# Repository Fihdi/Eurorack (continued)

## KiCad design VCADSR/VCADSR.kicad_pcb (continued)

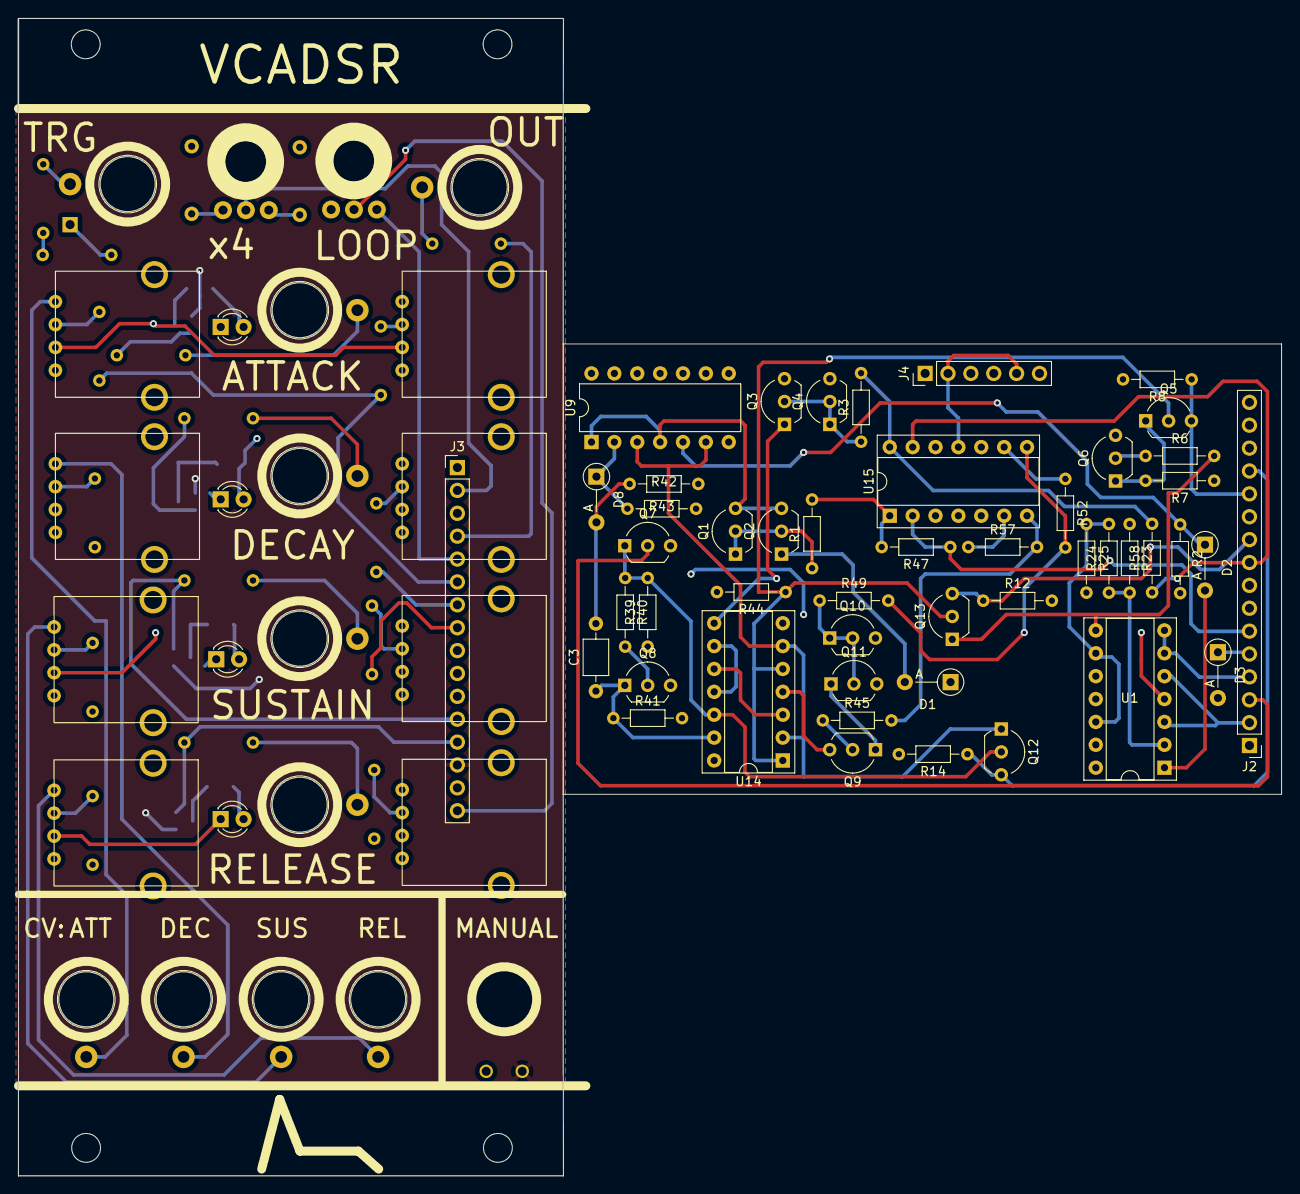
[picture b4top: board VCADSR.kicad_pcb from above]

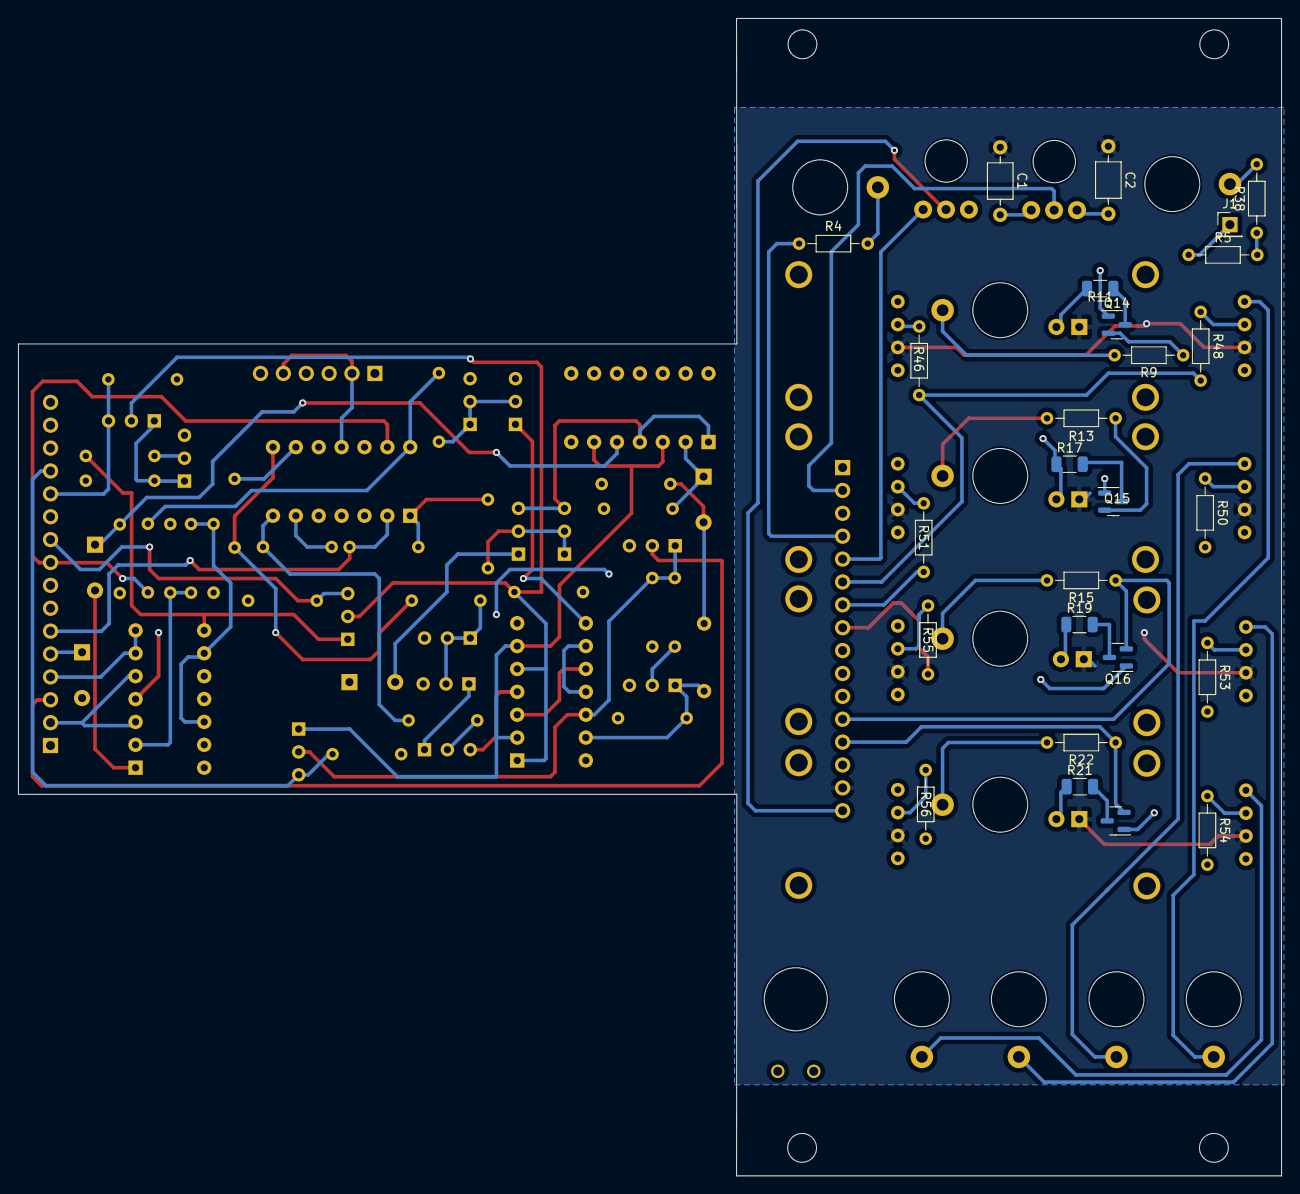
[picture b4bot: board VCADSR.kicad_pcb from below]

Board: 4 copper layers, 140.2 x 128.5 mm, 99 parts (26 on the bottom side), 72 nets.

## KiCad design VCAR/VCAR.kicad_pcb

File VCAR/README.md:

# 10hp Voltage controlled Attack and Release/Slew rate limiter

Voltage controlled SLEW Rate limiter / Attack/Release Module.

Can be used as an Envelope Generator, Slew Rate Limiter, VCO, LFO, Waveshaper, Gate Delay, Rythm Generator and a million other things.

Finally got this one working after 3 Revisions....

Schematic inspired by the legendary Dual Universal Slope Generator by Serge Tcherepnin, and later on Make Noise Maths, Befaco Rampage, Kassutronics Slope, etc.

One thing that could be added would be a jumper at the summing stage for the Rise (Attack) CV so that the feedback signal goes to either the first or second inverting stage ( the second inverter would then also be an inverting summing amplifier). This would give sharkfins instead of exponential spikes.

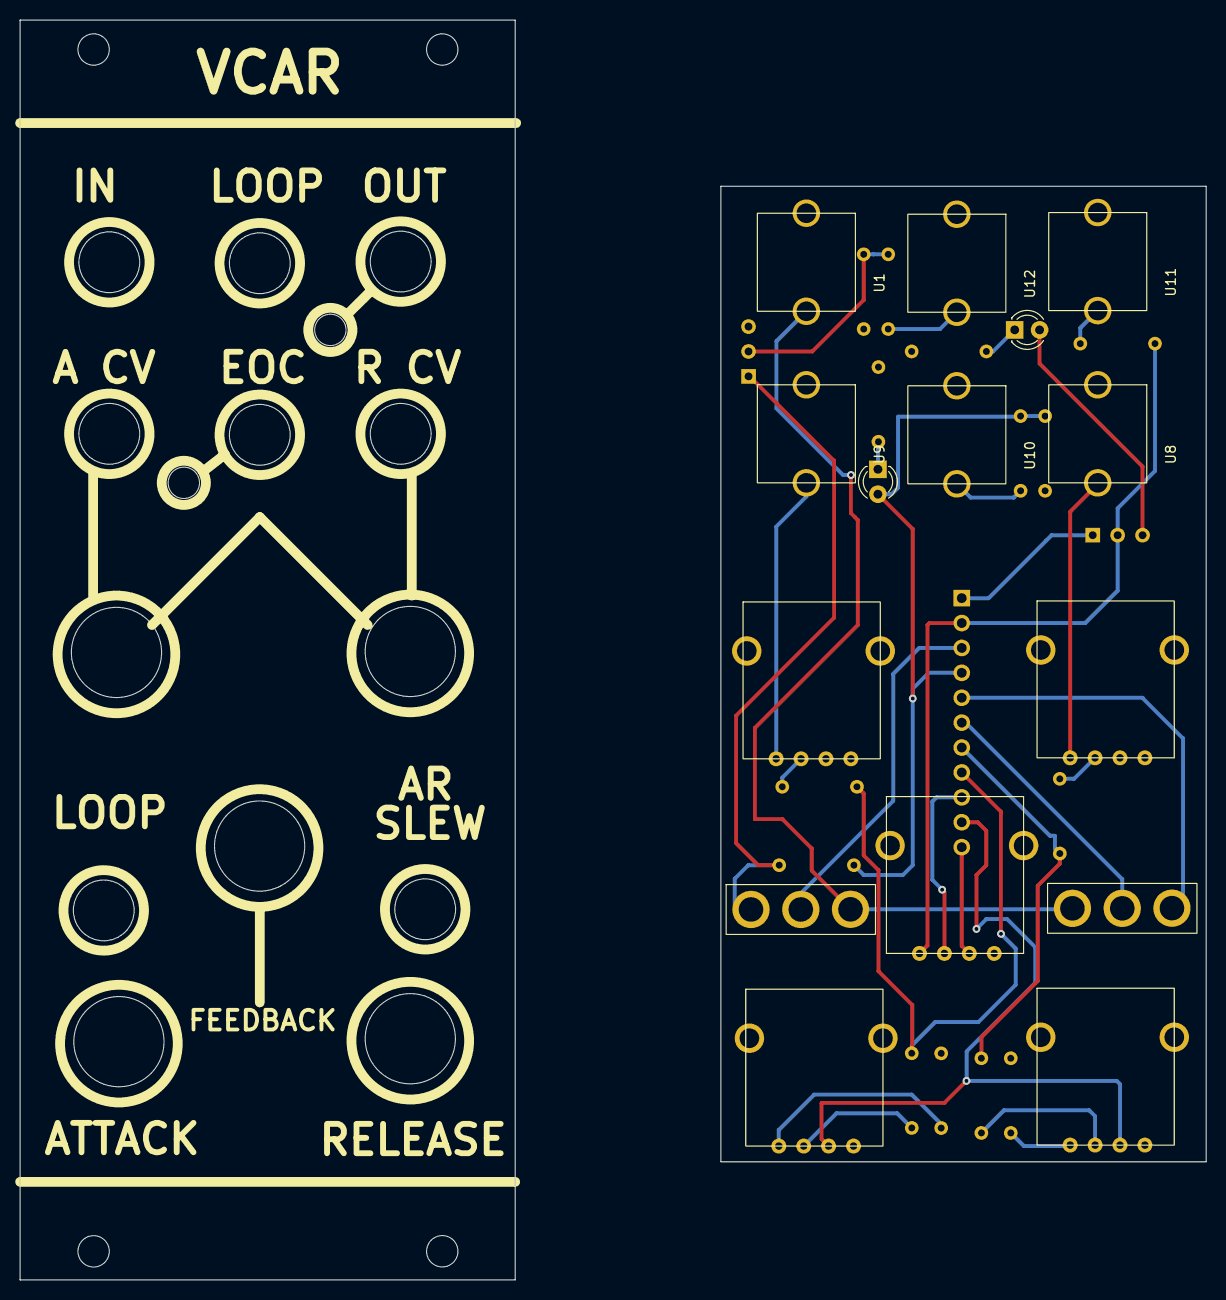
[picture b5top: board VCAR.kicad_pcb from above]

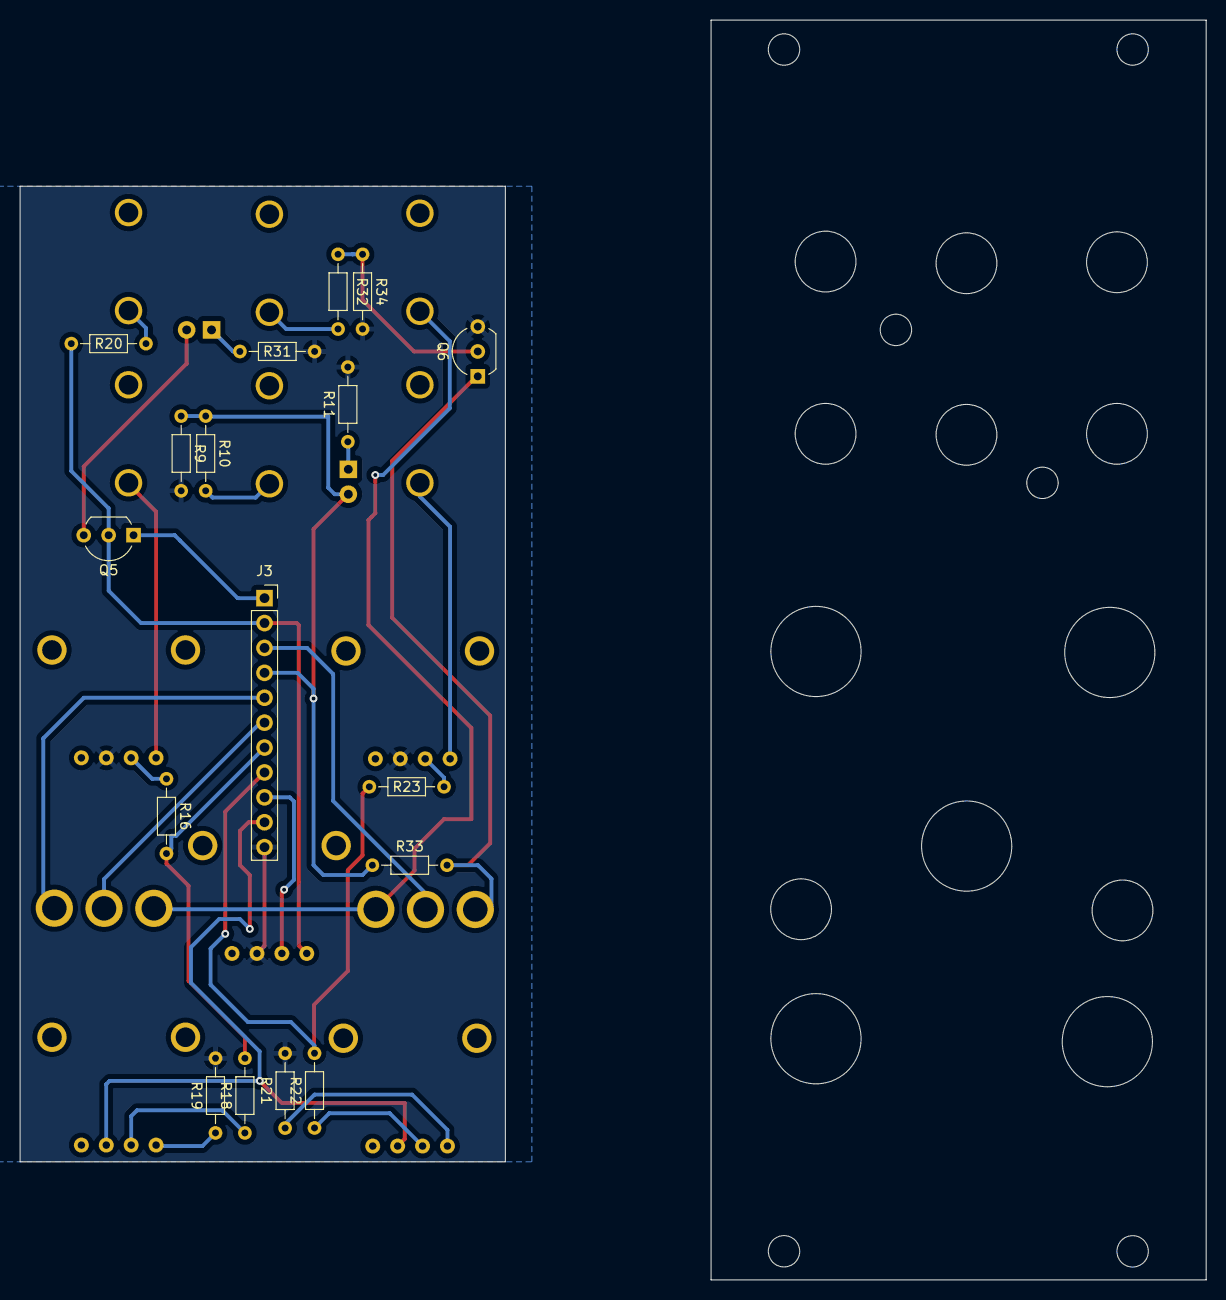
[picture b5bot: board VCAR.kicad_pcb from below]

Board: 2 copper layers, 49.5 x 99.5 mm, 32 parts (17 on the bottom side), 28 nets.

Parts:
D2, D7: LED; LED_D3.0mm
J3: Conn_01x11_Pin; PinSocket_1x11_P2.54mm_Vertical
Q5, Q6: BC547; TO-92_Inline_Wide
R9, R10, R11, R16, R18, R19, R20, R21, R22, R23, R31, R32, R33, R34: R; R_Axial_DIN0204_L3.6mm_D1.6mm_P7.62mm_Horizontal
RV1, RV2, RV3, RV4, RV5: R_Potentiometer; AlpsPot
U1, U8, U9, U10, U11, U12: Aux_flush; 3mm5 Mono Aux
U2, U7: Switch

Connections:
+12V: J3.1, Q5.1 (C)
-12V: J3.10, RV2.3, RV3.3
BUF_IN: J3.3, U7.2
EOC: D2.2 (A), J3.4, R9.1, R10.1, R33.1
FBO: J3.9, RV5.2
FF: J3.5, U2.3
GND: J3.11, Q6.3 (E), R9.2, R11.2, R19.2, R21.2, R31.2, R34.2, RV1.3, RV4.3, RV5.3
GOAL: J3.6, U2.2
IN: U1.1, U2.1, U7.3
unnamed: D2.1 (K), R11.1
unnamed: D7.2 (A), Q5.3 (E)
unnamed: D7.1 (K), R31.1
unnamed: Q6.2 (B), R32.1, R34.1
unnamed: Q6.1 (C), R33.2, U7.1
unnamed: R10.2, U10.1
unnamed: R16.1, RV1.2
unnamed: R18.1, RV2.2
unnamed: R19.1, RV2.1
unnamed: R20.2, U11.1
unnamed: R21.1, RV3.1
unnamed: R22.1, RV3.2
unnamed: R23.1, RV4.2
unnamed: R32.2, U12.1
unnamed: RV1.1, U8.1
unnamed: RV4.1, U9.1
OUT: J3.2, Q5.2 (B), R20.1, RV5.1
VGND1: J3.7, R16.2, R18.2
VGND2: J3.8, R22.2, R23.2

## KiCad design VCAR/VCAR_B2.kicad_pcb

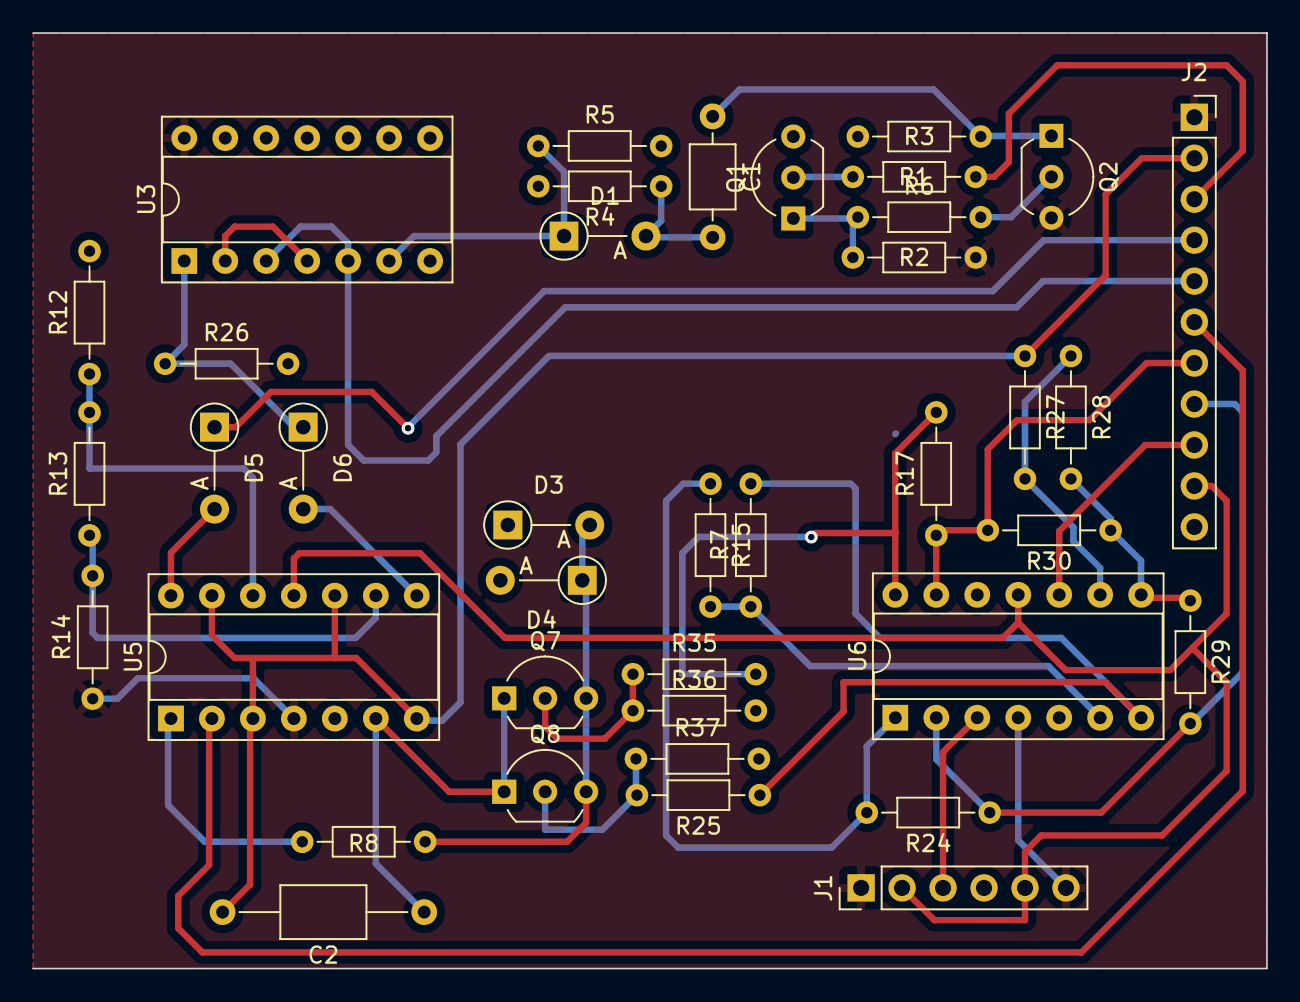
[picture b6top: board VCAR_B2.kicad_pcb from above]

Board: 2 copper layers, 76.5 x 58.0 mm, 39 parts (0 on the bottom side), 34 nets.

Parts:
C1: C; C_Axial_L3.8mm_D2.6mm_P7.50mm_Horizontal
C2: C; C_Axial_L5.1mm_D3.1mm_P12.50mm_Horizontal
D1, D3, D4, D5, D6: D; D_A-405_P5.08mm_Vertical_AnodeUp
J1: Conn_01x06_Pin; PinHeader_1x06_P2.54mm_Vertical
J2: Conn_01x11_Pin; PinSocket_1x11_P2.54mm_Vertical
Q1, Q8: BC547; TO-92_Inline_Wide
Q2, Q7: BC557; TO-92_Inline_Wide
R1, R2, R3, R4, R5, R6, R7, R8, R12, R13, R14, R15, R17, R24, R25, R26, R27, R28, R29, R30, R35, R36, R37: R; R_Axial_DIN0204_L3.6mm_D1.6mm_P7.62mm_Horizontal
U3: 4001; DIP-14_W7.62mm_Socket
U5, U6: TL074; DIP-14_W7.62mm_Socket

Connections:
+12V: J1.1, J1.6, J2.1, Q2.3 (E), R2.1, R14.1, U3.14 (VDD), U5.4 (V+), U6.4 (V+)
-12V: J1.2, J1.5, J2.10, U5.11 (V-), U6.11 (V-)
BUF_IN: J2.3, R1.2
EOC: D5.1 (K), J2.4
FBK: R28.2, R29.1, R30.1, U6.8
FBO: J2.9, U6.10 (+)
FCV: Q7.2 (B), R35.1, R36.1
FF: J2.5, U3.3, U3.5
GND: D3.1 (K), D4.2 (A), J1.3, J1.4, J2.11, Q1.3 (E), R3.2, R4.2, R5.2, R12.2, R26.2, R36.2, R37.2, U3.7 (VSS), U5.5 (+), U6.3 (+), U6.5 (+), U6.12 (+)
GOAL: J2.6, U5.2 (-)
HI: R13.1, R14.2, U5.9 (-)
LO: R12.1, R13.2, U5.12 (+)
unnamed: C1.2, D1.2 (A), R4.1
unnamed: D1.1 (K), R5.1, U3.6
unnamed: D3.2 (A), D4.1 (K), Q7.3 (E), Q8.3 (E), R8.2
unnamed: D5.2 (A), U5.14
unnamed: D6.2 (A), U5.8
unnamed: D6.1 (K), R26.1, U3.1
unnamed: Q1.2 (B), R1.1
unnamed: Q1.1 (C), R2.2, R6.1
unnamed: Q2.2 (B), R6.2
unnamed: C1.1, Q2.1 (C), R3.1
unnamed: C2.1, Q7.1 (C), Q8.1 (C), U5.6 (-)
unnamed: R8.1, U5.1
unnamed: R15.1, R24.2, U6.1
unnamed: R17.2, R35.2, U6.14
unnamed: R7.2, R25.1, U6.7
unnamed: U3.2, U3.4
unnamed: R7.1, R15.2, U6.6 (-)
unnamed: R27.2, R28.1, U6.9 (-)
OUT: C2.2, J2.2, R27.1, U5.3 (+), U5.7, U5.10 (+), U5.13 (-)
RCV: Q8.2 (B), R25.2, R37.1
VGND1: J2.7, R17.1, R30.2, U6.13 (-)
VGND2: J2.8, R24.1, R29.2, U6.2 (-)

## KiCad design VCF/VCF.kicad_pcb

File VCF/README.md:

Voltage controlled Filter.

A two-pole multimode Filter with Lowpass, Bandpass and Highpass outputs.

Ideas and Improvements:

5 minutes after ordering the VCF I, of course, got a great idea for a feature that I could have included: A Notch output.
By subtracting the bandpass output from the original signal you get an output with Notch-filter characteristics IN THEORY. I do not think it would work very well with just a simple subtractor circuit because of the phase shift between the bandpass and the original signal.

Using a VCA for CV-Resonance (Not necessary for me to be honest)

A clone of the VCF-3 by Skull and Circuits:
https://www.skullandcircuits.com/vcf-3/?v=d3dcf429c679

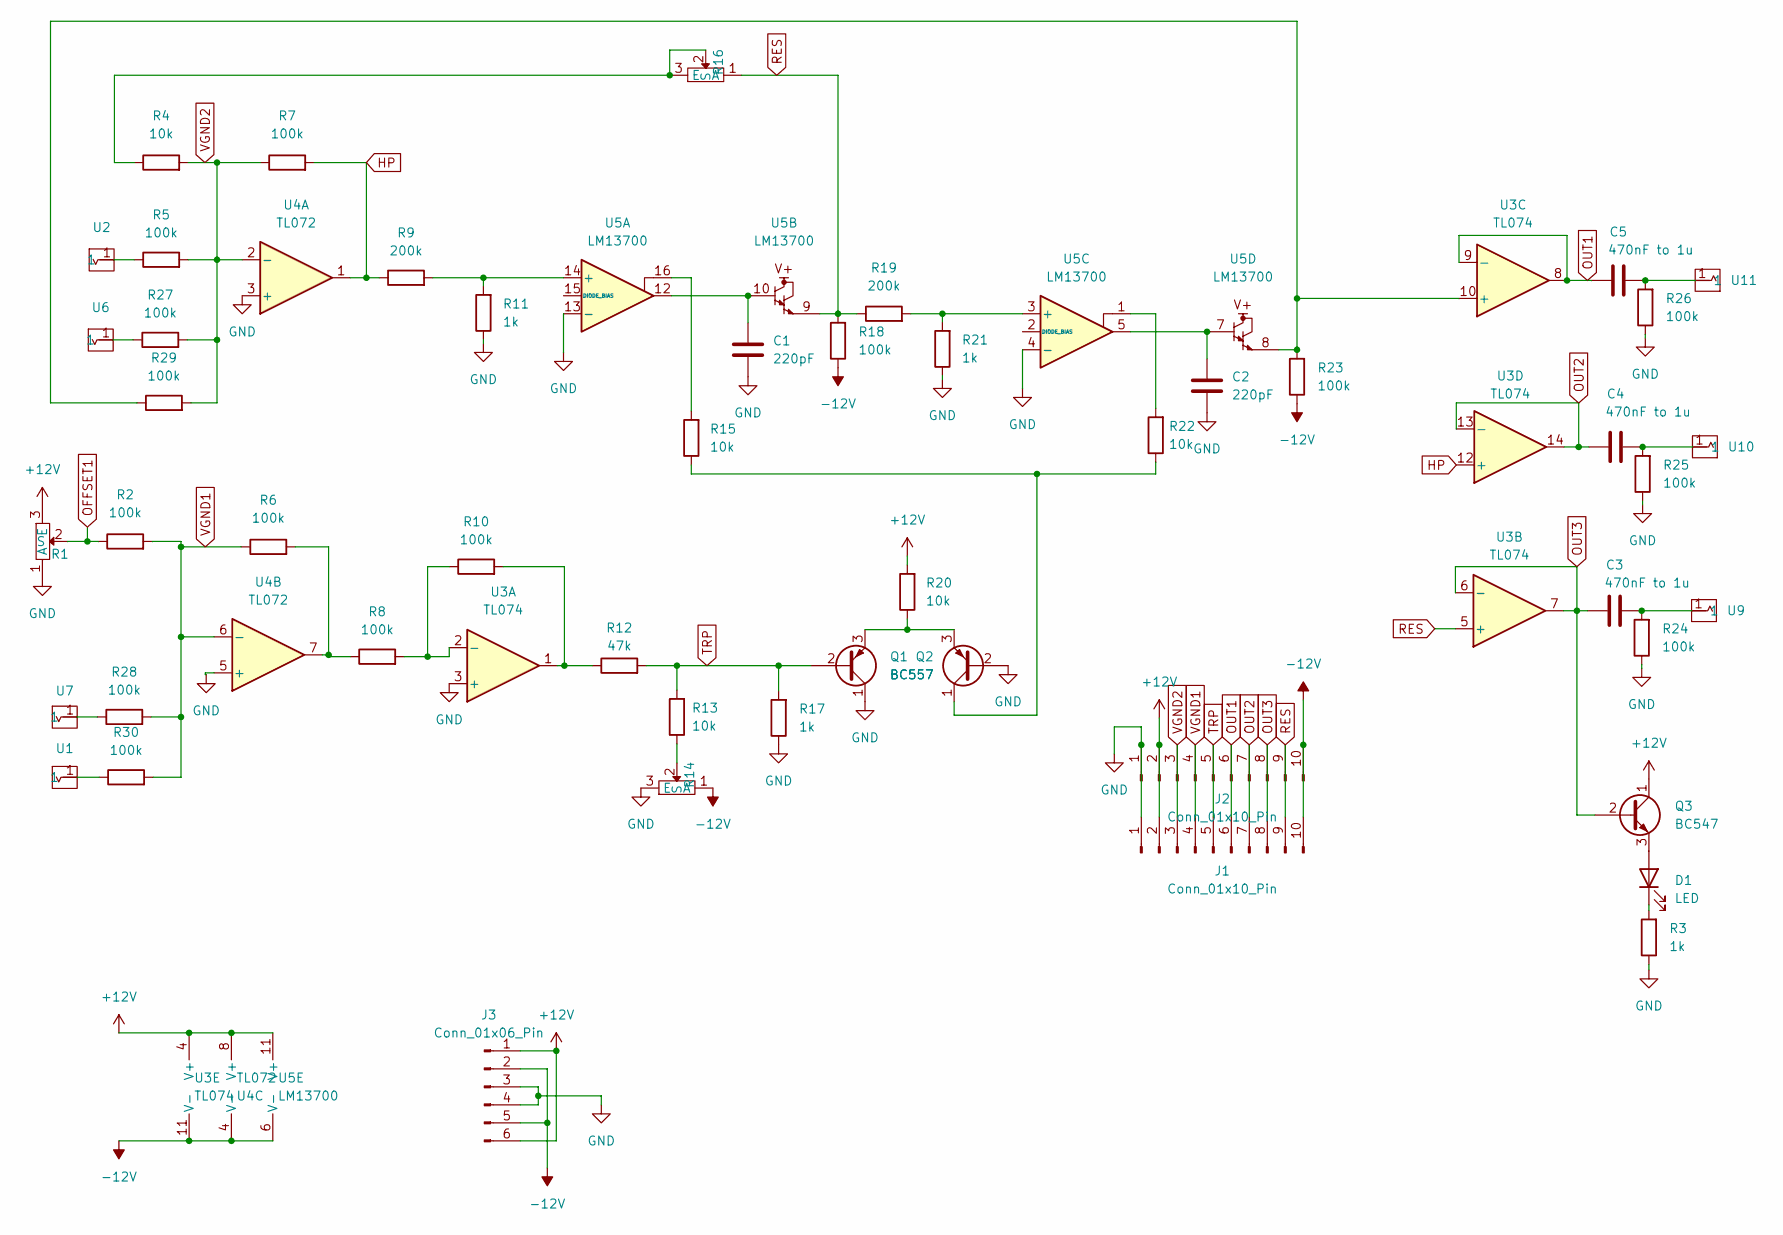
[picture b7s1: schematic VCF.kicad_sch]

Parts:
C1, C2: 220pF; C_Axial_L5.1mm_D3.1mm_P12.50mm_Horizontal
C3, C4, C5: 470nF to 1u; C_Axial_L5.1mm_D3.1mm_P12.50mm_Horizontal
D1: LED; LED_D5.0mm
J1, J2: Conn_01x10_Pin; PinHeader_1x10_P2.54mm_Vertical
J3: Conn_01x06_Pin; PinHeader_1x06_P2.54mm_Vertical
Q1, Q2: BC557; TO-92_Inline_Wide
Q3: BC547; TO-92L_Inline_Wide
R1, R14, R16: AlpsPot
R2, R5, R6, R7, R8, R10, R18, R23, R24, R25, R26, R27, R28, R29, R30: 100k; R_Axial_DIN0207_L6.3mm_D2.5mm_P10.16mm_Horizontal
R3, R11, R17, R21: 1k; R_Axial_DIN0207_L6.3mm_D2.5mm_P10.16mm_Horizontal
R4, R13, R15, R20, R22: 10k; R_Axial_DIN0207_L6.3mm_D2.5mm_P10.16mm_Horizontal
R9, R19: 200k; R_Axial_DIN0207_L6.3mm_D2.5mm_P10.16mm_Horizontal
R12: 47k; R_Axial_DIN0207_L6.3mm_D2.5mm_P10.16mm_Horizontal
U1, U2, U6, U7, U9, U10, U11: Aux_flush; 3mm5 Mono Aux
U3: TL074; DIP-14_W7.62mm
U4: TL072; DIP-8_W7.62mm
U5: LM13700; DIP-16_W7.62mm

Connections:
+12V: J1.2, J2.2, J3.1, J3.6, Q3.1 (C), R1.3 (E), R20.2, U3.4 (V+), U4.8 (V+), U5.11 (V+)
-12V: J1.10, J2.10, J3.2, J3.5, R14.1 (A), R18.1, R23.1, U3.11 (V-), U4.4 (V-), U5.6 (V-)
GND: C1.2, C2.2, J1.1, J2.1, J3.3, J3.4, Q1.1 (C), Q2.2 (B), R1.1 (A), R3.1, R11.1, R14.3 (E), R17.1, R21.1, R24.1, R25.1, R26.1, U3.3 (+), U4.3 (+), U4.5 (+), U5.4 (-), U5.13 (-)
HP: R7.2, R9.1, U3.12 (+), U4.1
unnamed: C1.1, U5.10, U5.12
unnamed: C2.1, U5.5, U5.7
unnamed: C3.2, R24.2, U9.1
unnamed: C4.2, R25.2, U10.1
unnamed: C5.2, R26.2, U11.1
unnamed: D1.2 (A), Q3.3 (E)
unnamed: D1.1 (K), R3.2
unnamed: Q1.3 (E), Q2.3 (E), R20.1
unnamed: Q2.1 (C), R15.1, R22.1
unnamed: R5.1, U2.1
unnamed: R6.2, R8.1, U4.7
unnamed: R10.2, R12.1, U3.1
unnamed: R13.1, R14.2 (S)
unnamed: R15.2, U5.16
unnamed: R4.1, R16.2 (S), R16.3 (E)
unnamed: R22.2, U5.1
unnamed: R27.1, U6.1
unnamed: R28.1, U7.1
unnamed: R30.1, U1.1
unnamed: R8.2, R10.1, U3.2 (-)
unnamed: R23.2, R29.1, U3.10 (+), U5.8
unnamed: R9.2, R11.2, U5.14 (+)
unnamed: R19.2, R21.2, U5.3 (+)
OFFSET1: R1.2 (S), R2.1
OUT1: C5.1, J1.6, J2.6, U3.8, U3.9 (-)
OUT2: C4.1, J1.7, J2.7, U3.13 (-), U3.14
OUT3: C3.1, J1.8, J2.8, Q3.2 (B), U3.6 (-), U3.7
RES: J1.9, J2.9, R16.1 (A), R18.2, R19.1, U3.5 (+), U5.9
TRP: J1.5, J2.5, Q1.2 (B), R12.2, R13.2, R17.2
VGND1: J1.4, J2.4, R2.2, R6.1, R28.2, R30.2, U4.6 (-)
VGND2: J1.3, J2.3, R4.2, R5.2, R7.1, R27.2, R29.2, U4.2 (-)

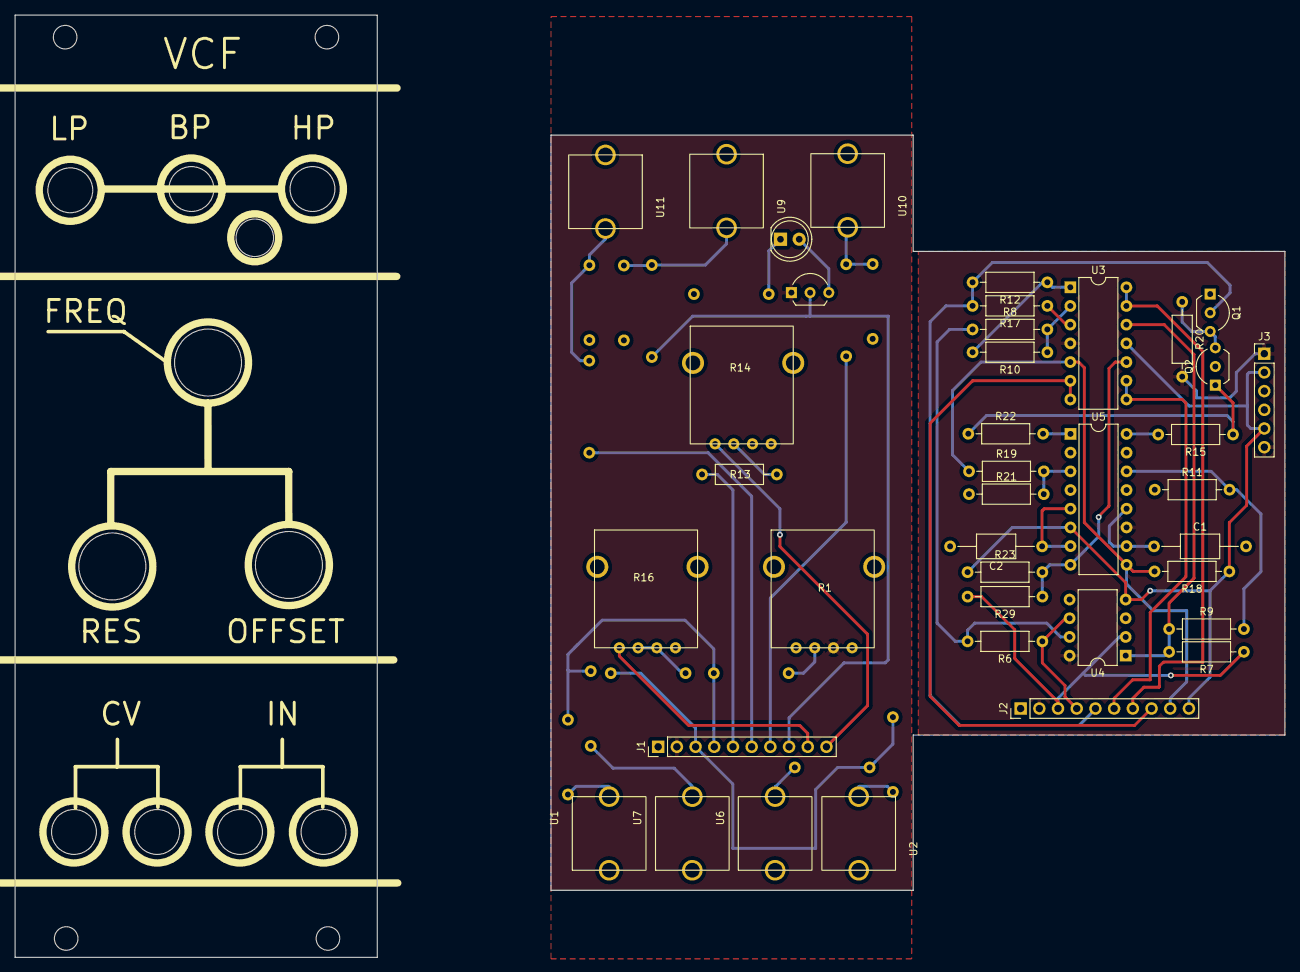
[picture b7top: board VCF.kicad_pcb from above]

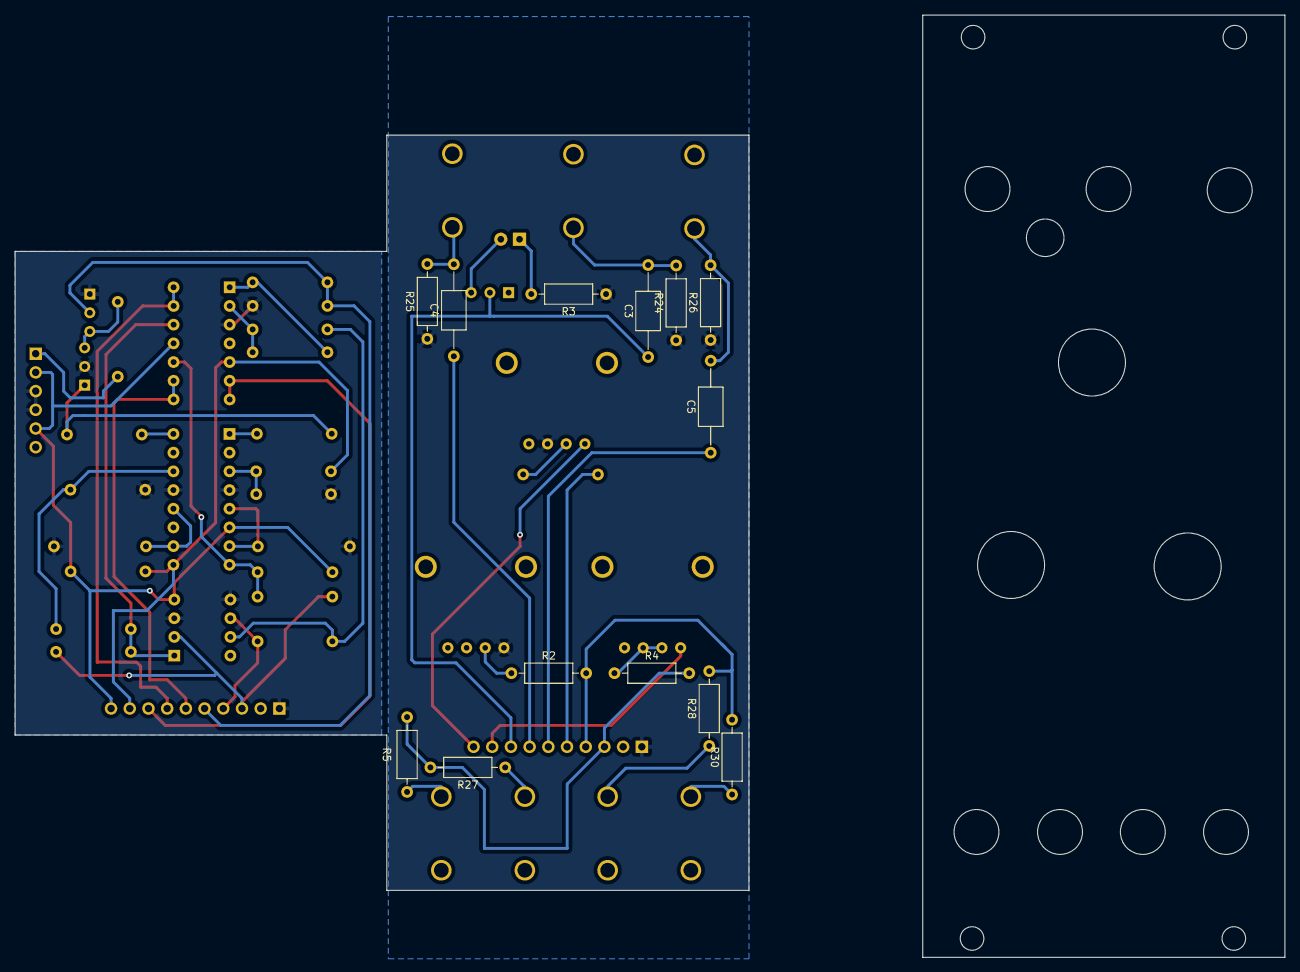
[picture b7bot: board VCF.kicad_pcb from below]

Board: 2 copper layers, 99.7 x 102.6 mm, 52 parts (13 on the bottom side), 35 nets.
